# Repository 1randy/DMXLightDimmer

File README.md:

# DMXLightDimmer

A ESP8266 based 4 Channel DMX dimmer with countdown function (2h, 4h, 6h & 8h) for Dimmerpacks

Used for illumination in Bird Cages

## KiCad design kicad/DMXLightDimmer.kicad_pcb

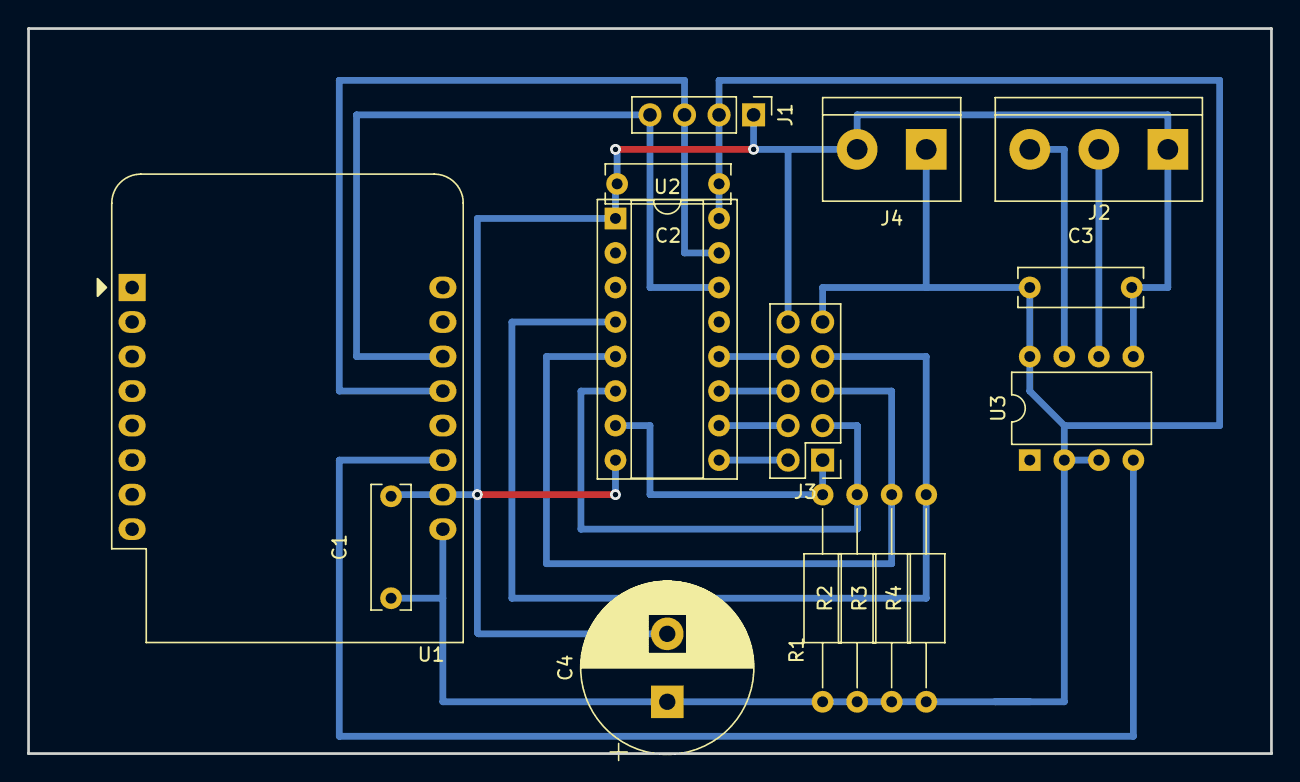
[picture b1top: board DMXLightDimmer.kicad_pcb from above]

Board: 2 copper layers, 91.4 x 53.3 mm, 15 parts (0 on the bottom side), 15 nets.

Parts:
C1, C2, C3: 100n; C_Rect_L9.0mm_W2.7mm_P7.50mm_MKT
C4: 220u; CP_Radial_D12.5mm_P5.00mm
J1: I2C LCD1602; PinHeader_1x04_P2.54mm_Vertical
J2: DMX; TerminalBlock_bornier-3_P5.08mm
J3: Switches; PinHeader_2x05_P2.54mm_Vertical
J4: PWR; TerminalBlock_bornier-2_P5.08mm
R1, R2, R3, R4: 4k7; R_Axial_DIN0207_L6.3mm_D2.5mm_P15.24mm_Horizontal
U1: WeMos_D1_mini; WEMOS_D1_mini_light
U2: PCF8574A; DIP-16_W7.62mm_Socket
U3: SN75176AP; DIP-8_W7.62mm

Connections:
+5V: C1.1, C2.1, C3.1, C4.1, J1.2, J3.9, J4.1, R1.1, R2.1, R3.1, R4.1, U1.9, U2.16, U3.2, U3.3, U3.8
GND: C1.2, C2.2, C3.2, C4.2, J1.1, J2.1, J3.10, J4.2, U1.10, U2.1, U2.8, U3.5
unnamed: J1.3, U1.13, U2.15
unnamed: J1.4, U1.14, U2.14
unnamed: J2.2, U3.6
unnamed: J2.3, U3.7
unnamed: J3.1, R1.2, U2.7
unnamed: J3.2, U2.9
unnamed: J3.3, R2.2, U2.6
unnamed: J3.4, U2.10
unnamed: J3.5, R3.2, U2.5
unnamed: J3.6, U2.11
unnamed: J3.7, R4.2, U2.4
unnamed: J3.8, U2.12
unnamed: U1.11, U3.4
